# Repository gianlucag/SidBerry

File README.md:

## SidBerry ##
### Music player per chip SID 6581 realizzato con RaspberryPi ###

Un SID jukebox realizzato con RasberryPi e il SID chip originale 6581. Il chip è alloggiato in una board custom collegata direttamente ai GPIO del Rasberry!

La board può riprodurre qualsiasi SID file, basta caricare i file .sid nella sdcard del Rasberry, avviare il player e collegare all'uscita jack un paio di casse preamplificate o meglio uno stereo.

### SID chip ###

Il SID originale, nelle varianti 6581 e 8580, è controllato caricando i suoi 29 registri interni con i valori opportuni al momento opportuno. La sequenza di byte inviati genera l'effetto o la musica desiderati. Ogni registro è 1 byte ed i registri sono in tutto 29 quindi c'è bisogno di almeno 5 gpio di indirizzo (2^5=32) e 8 gpio di dati per un totale di 13 gpio. Un altro gpio è richiesto per la linea CS del chip (Chip Select).

Fortunatamente il Raspberry ha ben 17 gpio e i 14 richiesti sono perfettamente pilotabili con la libreria WiringPi. Gli altri pin del chip servono per i due condensatori dei filtri interni (CAP_a e CAP_b), alimentazione, linea R/W (che andremo a collegare direttamente a GND, siamo sempre in scrittura), entrata del segnale di clock, linea di reset (collegata sempre a VCC) e uscita audio analogica (AUDIO OUT).

Ecco la configurazione dei registri interni del SID:

Qui per una descrizione più dettagliata del funzionamento interno del chip:

http://www.waitingforfriday.com/index.php/Commodore_SID_6581_Datasheet

### Hardware ###

La board riproduce esattamente le "condizioni al contorno" per il SID chip come se si trovasse alloggiato in un Commodore 64 originale. L'application note originale mostra chiaramente i collegamenti da effettuare e i pochi componenti esterni richiesti (generatore di clock, condensatori e poco altro).

Unica differenza, le linee di indirizzo e dati vengono dirottate direttamente sui gpio del RasberryPi.

NOTA IMPORTANTE!: Il RasberryPi ragiona in logica CMOS a 3.3V mentre il SID chip è TTL a 5V quindi completamente incompatibili a livello di tensioni. Fortunatamente, siccome andiamo unicamente a scrivere nei registri, il RasberryPi dovrà soltanto applicare 3.3v ai capi del chip, più che sufficienti per essere interpretati come livello logico alto dal SID.

Lo schematico completo:

### Software ###

Il grosso del lavoro. Volevo una soluzione completamente stand-alone, senza l'ausilio di player esterni (come ACID64) e quindi ho realizzato un player che emula gran parte di un C64 originale. L'emulatore è necessario in quanto i file .sid sono programmi in linguaggio macchina 6502 e come tali devono essere eseguiti. Il player è scritto in C/C++ e basato sul mio emulatore MOS CPU 6502   più un semplice array di 65535 byte come memoria RAM (il C64 originale ha infatti 64K di RAM). Il player carica il codice programma contenuto nel file .sid nella RAM virtuale più un codice assembly aggiuntivo che ho chiamato micro-player: sostanzialmente si tratta di un programma minimale scritta in linguaggio macchina per CPU 6502 che assolve a due compiti specifici:

 * installare i vettori di reset e interrupt alle locazioni corrette
 * chiamare la play routine del codice sid ad ogni interrupt

Questo perchè il codice che genera la musica in un comune C64 è una funzione chiamata ad intervalli regolari (50 volte al secondo, 50Hz). La chiamata è effettuata per mezzo di un interrupt esterno. In questo modo è possibile avere musica e un qualsiasi altro programma (videogioco ad esempio) in esecuzione nello stesso momento.

Altre componenti sono il parser per i file .sid e la libreria WiringPi per pilotare i GPIO del RaspberryPi.

Questo il layout dell'intero applicativo, a destra è la memoria RAM virtuale 64K

Questo è il codice assembler del micro-player:

```
// istallazione del vettore di reset (0x0000)
memory[0xFFFD] = 0x00;
memory[0xFFFC] = 0x00;</p>
// istallazione del vettore di interrupt, punta alla play routine (0x0013)
memory[0xFFFF] = 0x00;
memory[0xFFFE] = 0x13;

// codice del micro-player
memory[0x0000] = 0xA9;
memory[0x0001] = atoi(argv[2]); // il registro A viene caricato con il numero della traccia (0-16)

memory[0x0002] = 0x20; // salta alla init-routine nel codice sid
memory[0x0003] = init &amp; 0xFF; // lo addr
memory[0x0004] = (init &gt;&gt; 8) &amp; 0xFF; // hi addr

memory[0x0005] = 0x58; // abilitiamo gli interrupt
memory[0x0006] = 0xEA; // nop
memory[0x0007] = 0x4C; // loop infinito
memory[0x0008] = 0x06;
memory[0x0009] = 0x00;

// Interrupt service routine (ISR)
memory[0x0013] = 0xEA; // nop
memory[0x0014] = 0xEA; // nop
memory[0x0015] = 0xEA; // nop
memory[0x0016] = 0x20; // saltiamo alla play routine
memory[0x0017] = play &amp; 0xFF;
memory[0x0018] = (play &gt;&gt; 8) &amp; 0xFF;
memory[0x0019] = 0xEA; // nop
memory[0x001A] = 0x40; // return from interrupt
```
### Modifiche al Software introdotte da Alessio Lombardo ###
- Bug-Fixing (si ringrazia Thoroide, https://www.gianlucaghettini.net/sidberry2-raspberry-pi-6581-sid-player/)
- Possibilità di compilare il sorgente per diverse schede/SoC. Oltre a RaspberryPI, è direttamente supportata la scheda Acme Systems AriettaG25. Altre schede possono essere aggiunte editando opportunamente i file "gpioInterface.cpp" e "gpioInterface.h". Se necessario, è possibile fare riferimento a librerie esterne per la gestione delle porte GPIO (ad esempio, "wiringPi" nel caso di Rapsberry o "wiringSam" nel caso di Arietta).
- Aggiunti controlli al player: Pausa/Continua, traccia precedente/successiva, Restart, Uscita (con reset dei registri), Modalità Verbose.

Per la scheda AriettaG25 con libreria "wiringSAM" già installata compilare con:
```
g++ *.cpp -D BOARD='ARIETTAG25' -o sidberry -lwiringSam
```
Per la scheda RaspberryPI con libreria "wiringPi" già installata compilare con:
```
g++ *.cpp -D BOARD='RASPBERRYPI' -o sidberry -lwiringPi
```
Per altre schede, dopo aver opportunamente modificato "gpioInterface.cpp" e "gpioInterface.h", compilare con:
```
g++ *.cpp -D BOARD='CUSTOM' -o sidberry
```

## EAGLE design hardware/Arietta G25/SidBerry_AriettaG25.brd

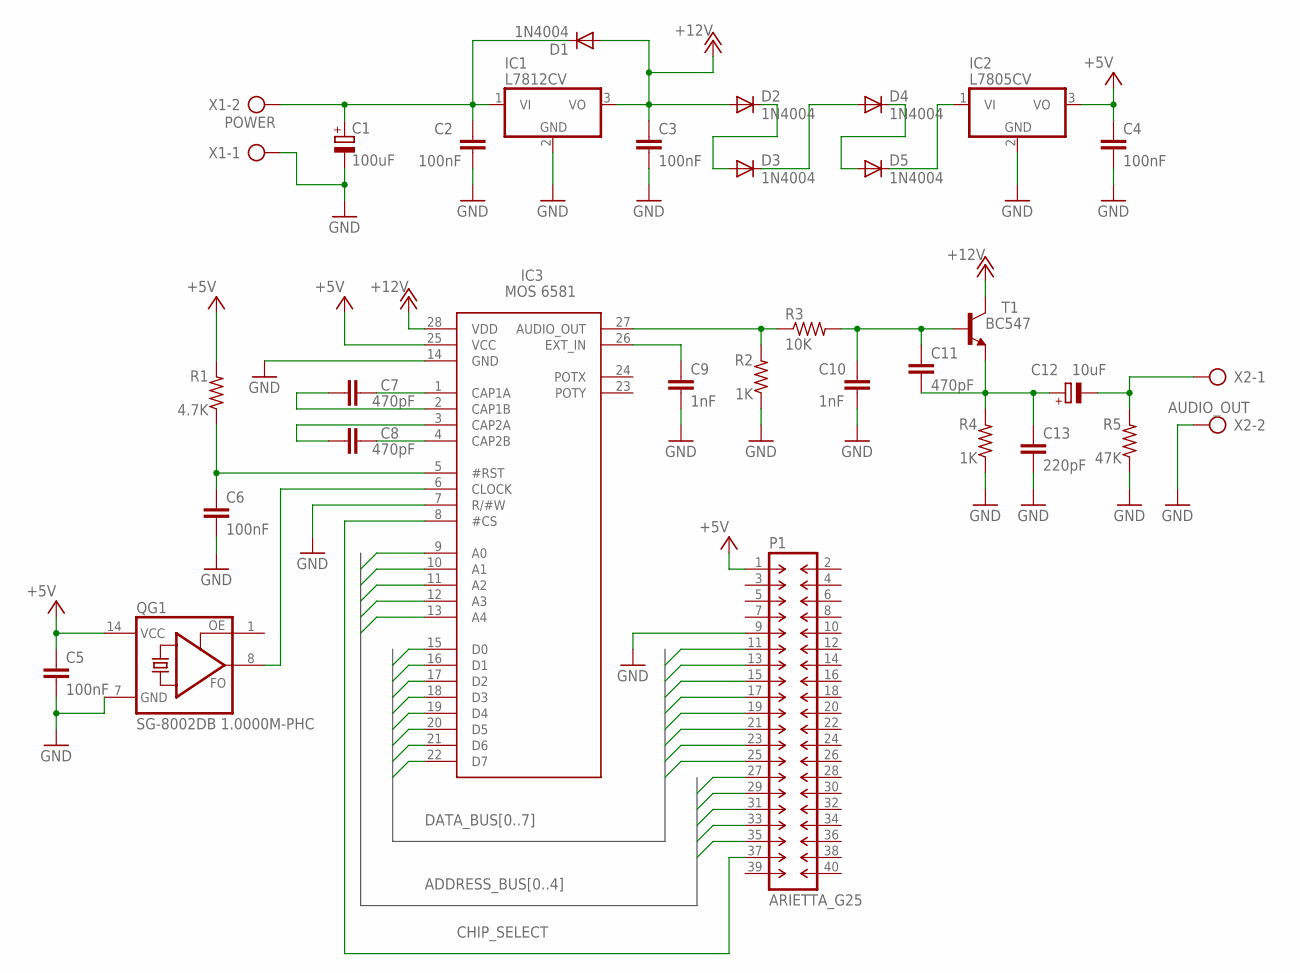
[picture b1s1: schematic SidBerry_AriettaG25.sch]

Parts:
C1: 100uF; E2,5-6
C2, C3, C4, C5, C6: 100nF; C025-024X044
C7, C8, C11: 470pF; C025-024X044
C9, C10: 1nF; C025-024X044
C12: 10uF; E2,5-5
C13: 220pF; C025-024X044
D1, D2, D3, D4, D5: 1N4004; DO41-10
IC1: L7812CV; TO220V
IC2: L7805CV; TO220V
IC3: MOS 6581; DIL28-6
P1: ARIETTA_G25; DIL-100-2X20
QG1: SG-8002DB 1.0000M-PHC; SG51
R1: 4.7K; 0207/10
R2, R4: 1K; 0207/10
R3: 10K; 0207/10
R5: 47K; 0207/10
T1: BC547; TO92-CBE
X1: POWER; AK500/2
X2: AUDIO_OUT; AK500/2

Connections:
+5V: C4.1, C5.1, IC2.3 (VO), IC3.25 (VCC), P1.1, QG1.14 (VCC), R1.2
+12V: C3.1, D1.A, D2.A, IC1.3 (VO), IC3.28 (VDD), T1.C
ADDRESS_BUS0: IC3.9 (A0), P1.27
ADDRESS_BUS1: IC3.10 (A1), P1.29
ADDRESS_BUS2: IC3.11 (A2), P1.31
ADDRESS_BUS3: IC3.12 (A3), P1.33
ADDRESS_BUS4: IC3.13 (A4), P1.35
CHIP_SELECT: IC3.8 (#CS), P1.37
DATA_BUS0: IC3.15 (D0), P1.25
DATA_BUS1: IC3.16 (D1), P1.23
DATA_BUS2: IC3.17 (D2), P1.21
DATA_BUS3: IC3.18 (D3), P1.19
DATA_BUS4: IC3.19 (D4), P1.17
DATA_BUS5: IC3.20 (D5), P1.15
DATA_BUS6: IC3.21 (D6), P1.13
DATA_BUS7: IC3.22 (D7), P1.11
GND: C1.-, C2.2, C3.2, C4.2, C5.2, C6.2, C9.2, C10.2, C13.2, IC1.2 (GND), IC2.2 (GND), IC3.7 (R/#W), IC3.14 (GND), P1.9, QG1.7 (GND), R2.1, R4.1, R5.1, X1.1, X2.2
unnamed: IC3.6 (CLOCK), QG1.8 (FO)
unnamed: C9.1, IC3.26 (EXT_IN)
unnamed: D2.C, D3.A
unnamed: D3.C, D4.A
unnamed: D4.C, D5.A
unnamed: D5.C, IC2.1 (VI)
unnamed: C8.2, IC3.4 (CAP2B)
unnamed: C8.1, IC3.3 (CAP2A)
unnamed: C7.1, IC3.2 (CAP1B)
unnamed: C7.2, IC3.1 (CAP1A)
unnamed: C6.1, IC3.5 (#RST), R1.1
unnamed: IC3.27 (AUDIO_OUT), R2.2, R3.1
unnamed: C1.+, C2.1, D1.C, IC1.1 (VI), X1.2
unnamed: C12.-, R5.2, X2.1
unnamed: C10.1, C11.1, R3.2, T1.B
unnamed: C11.2, C12.+, C13.1, R4.2, T1.E

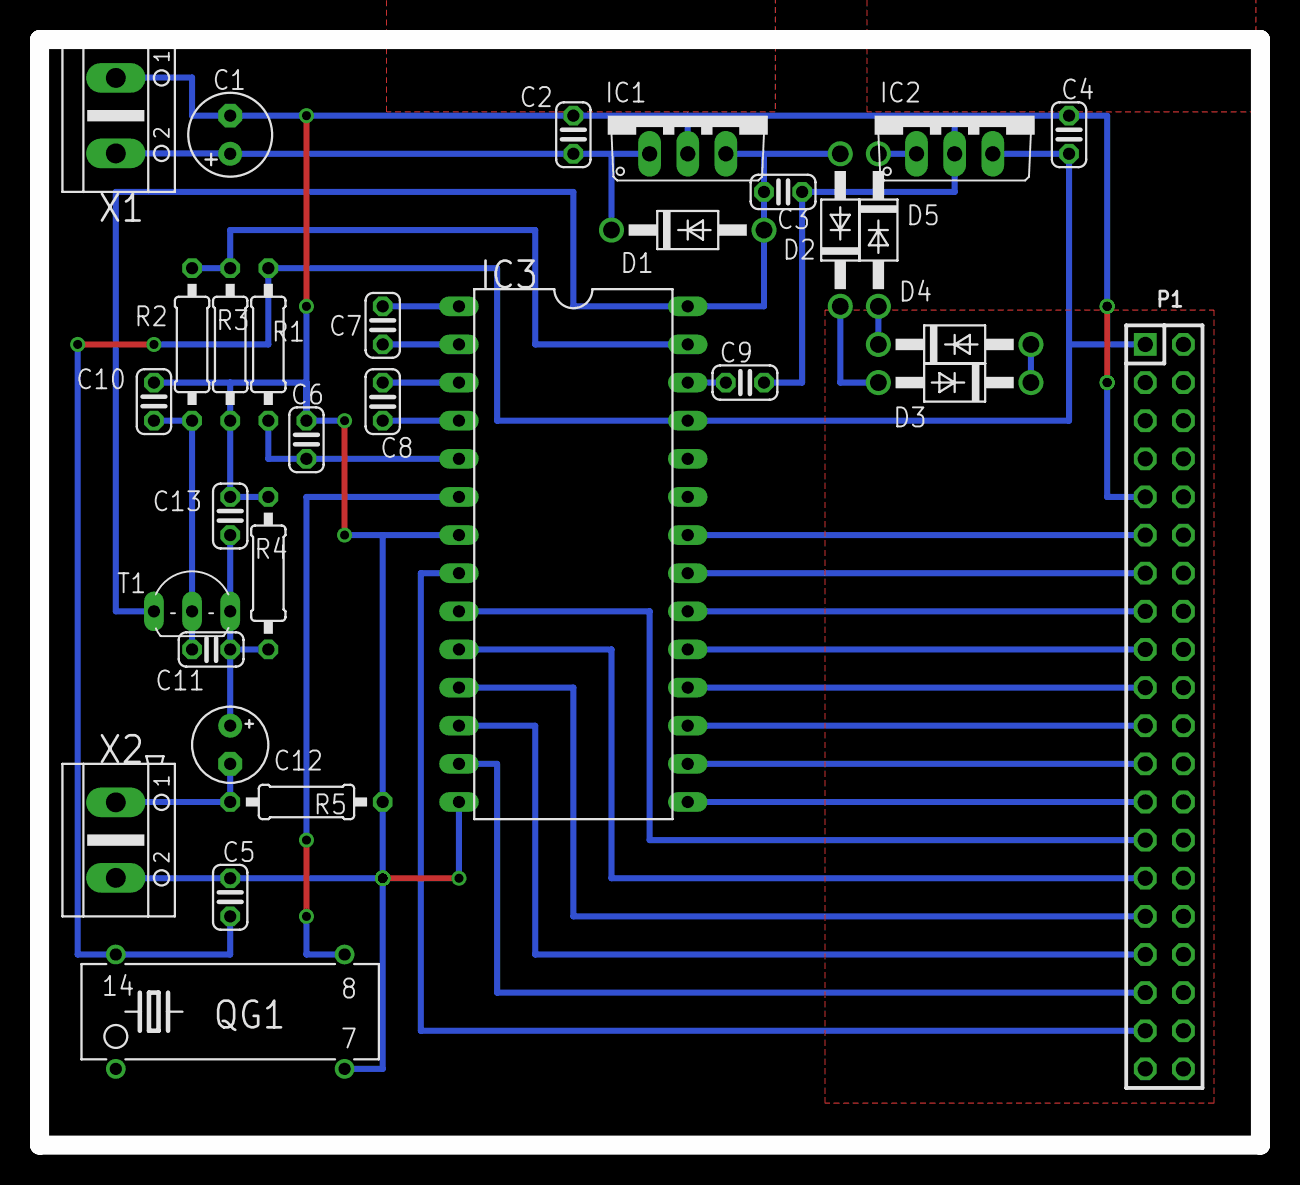
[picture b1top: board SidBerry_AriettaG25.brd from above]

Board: 2 copper layers, 81.3 x 73.6 mm, 32 parts (0 on the bottom side), 33 nets.

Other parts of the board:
U$1: A4L-LOC

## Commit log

2015-07-04 Sidberry SID player for raspberryPi
2015-07-04 images
2020-07-12 Interface to support different systems (RaspberryPi, AriettaG25, Custom Board).
2020-07-30 Player Update
2020-07-31 Update Sid Player
2020-08-05 Add schematics and boards
2020-08-05 scaled images

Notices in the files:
parts and their libraries:
con-headers-jp: Copyright (C) 2008, Bob Starr
